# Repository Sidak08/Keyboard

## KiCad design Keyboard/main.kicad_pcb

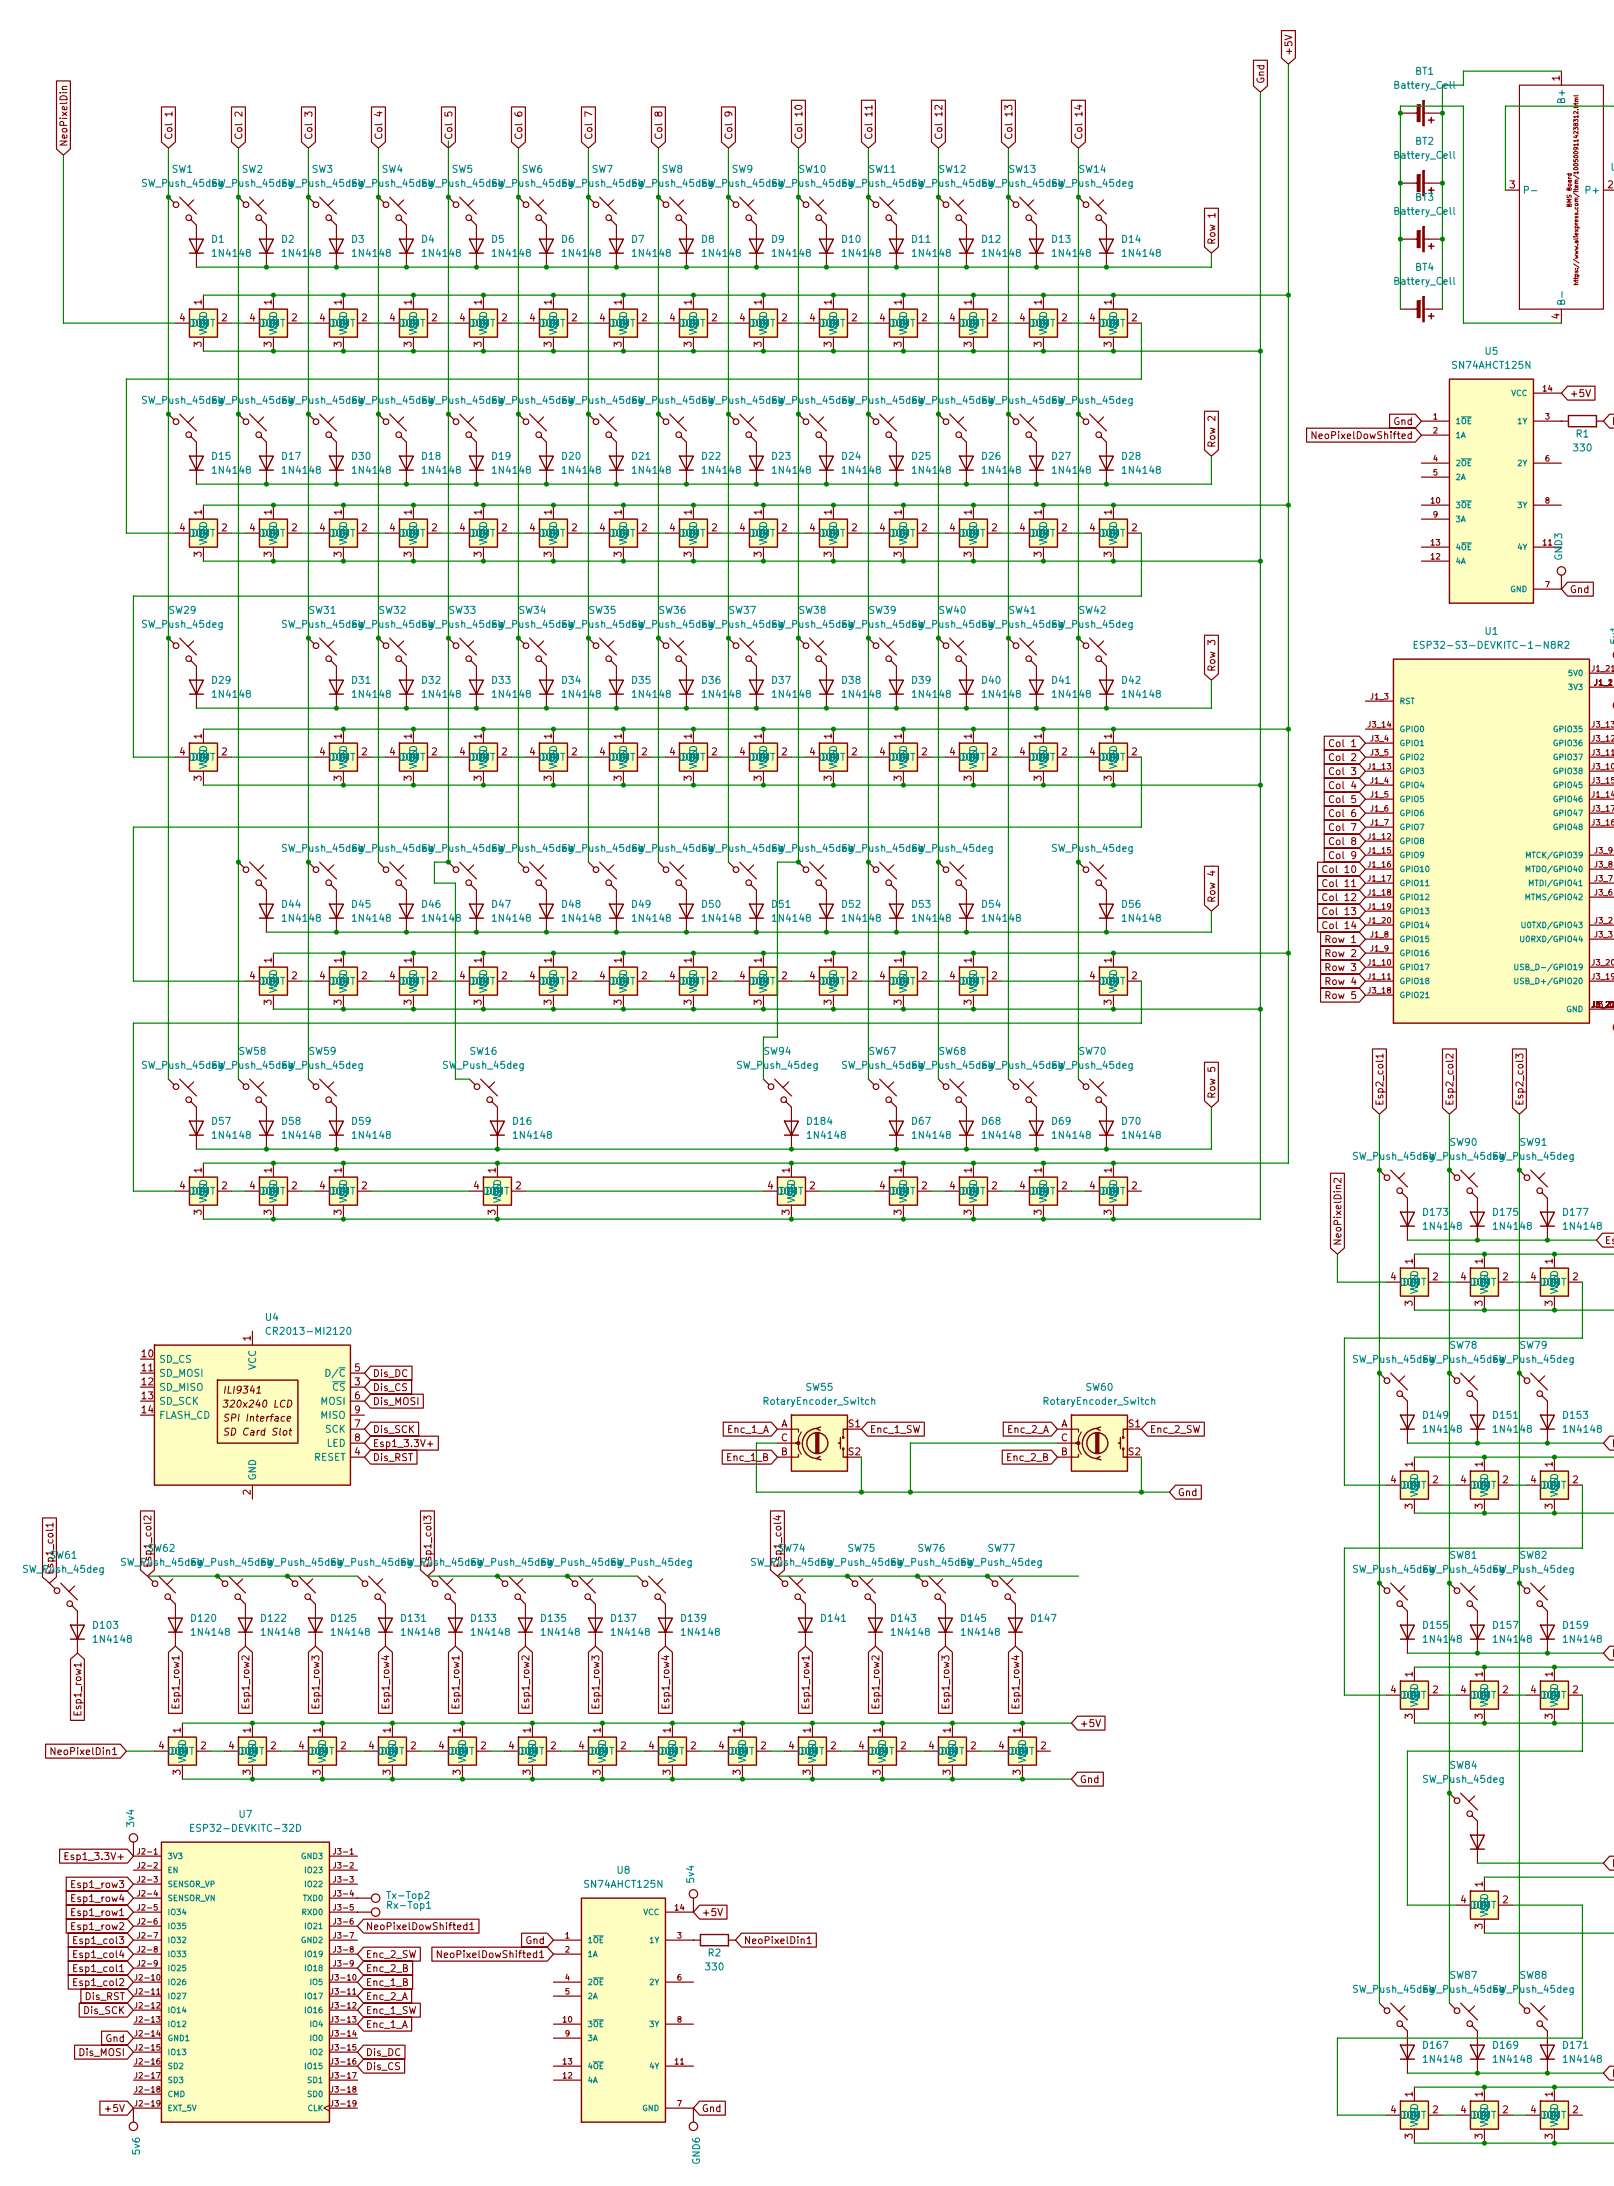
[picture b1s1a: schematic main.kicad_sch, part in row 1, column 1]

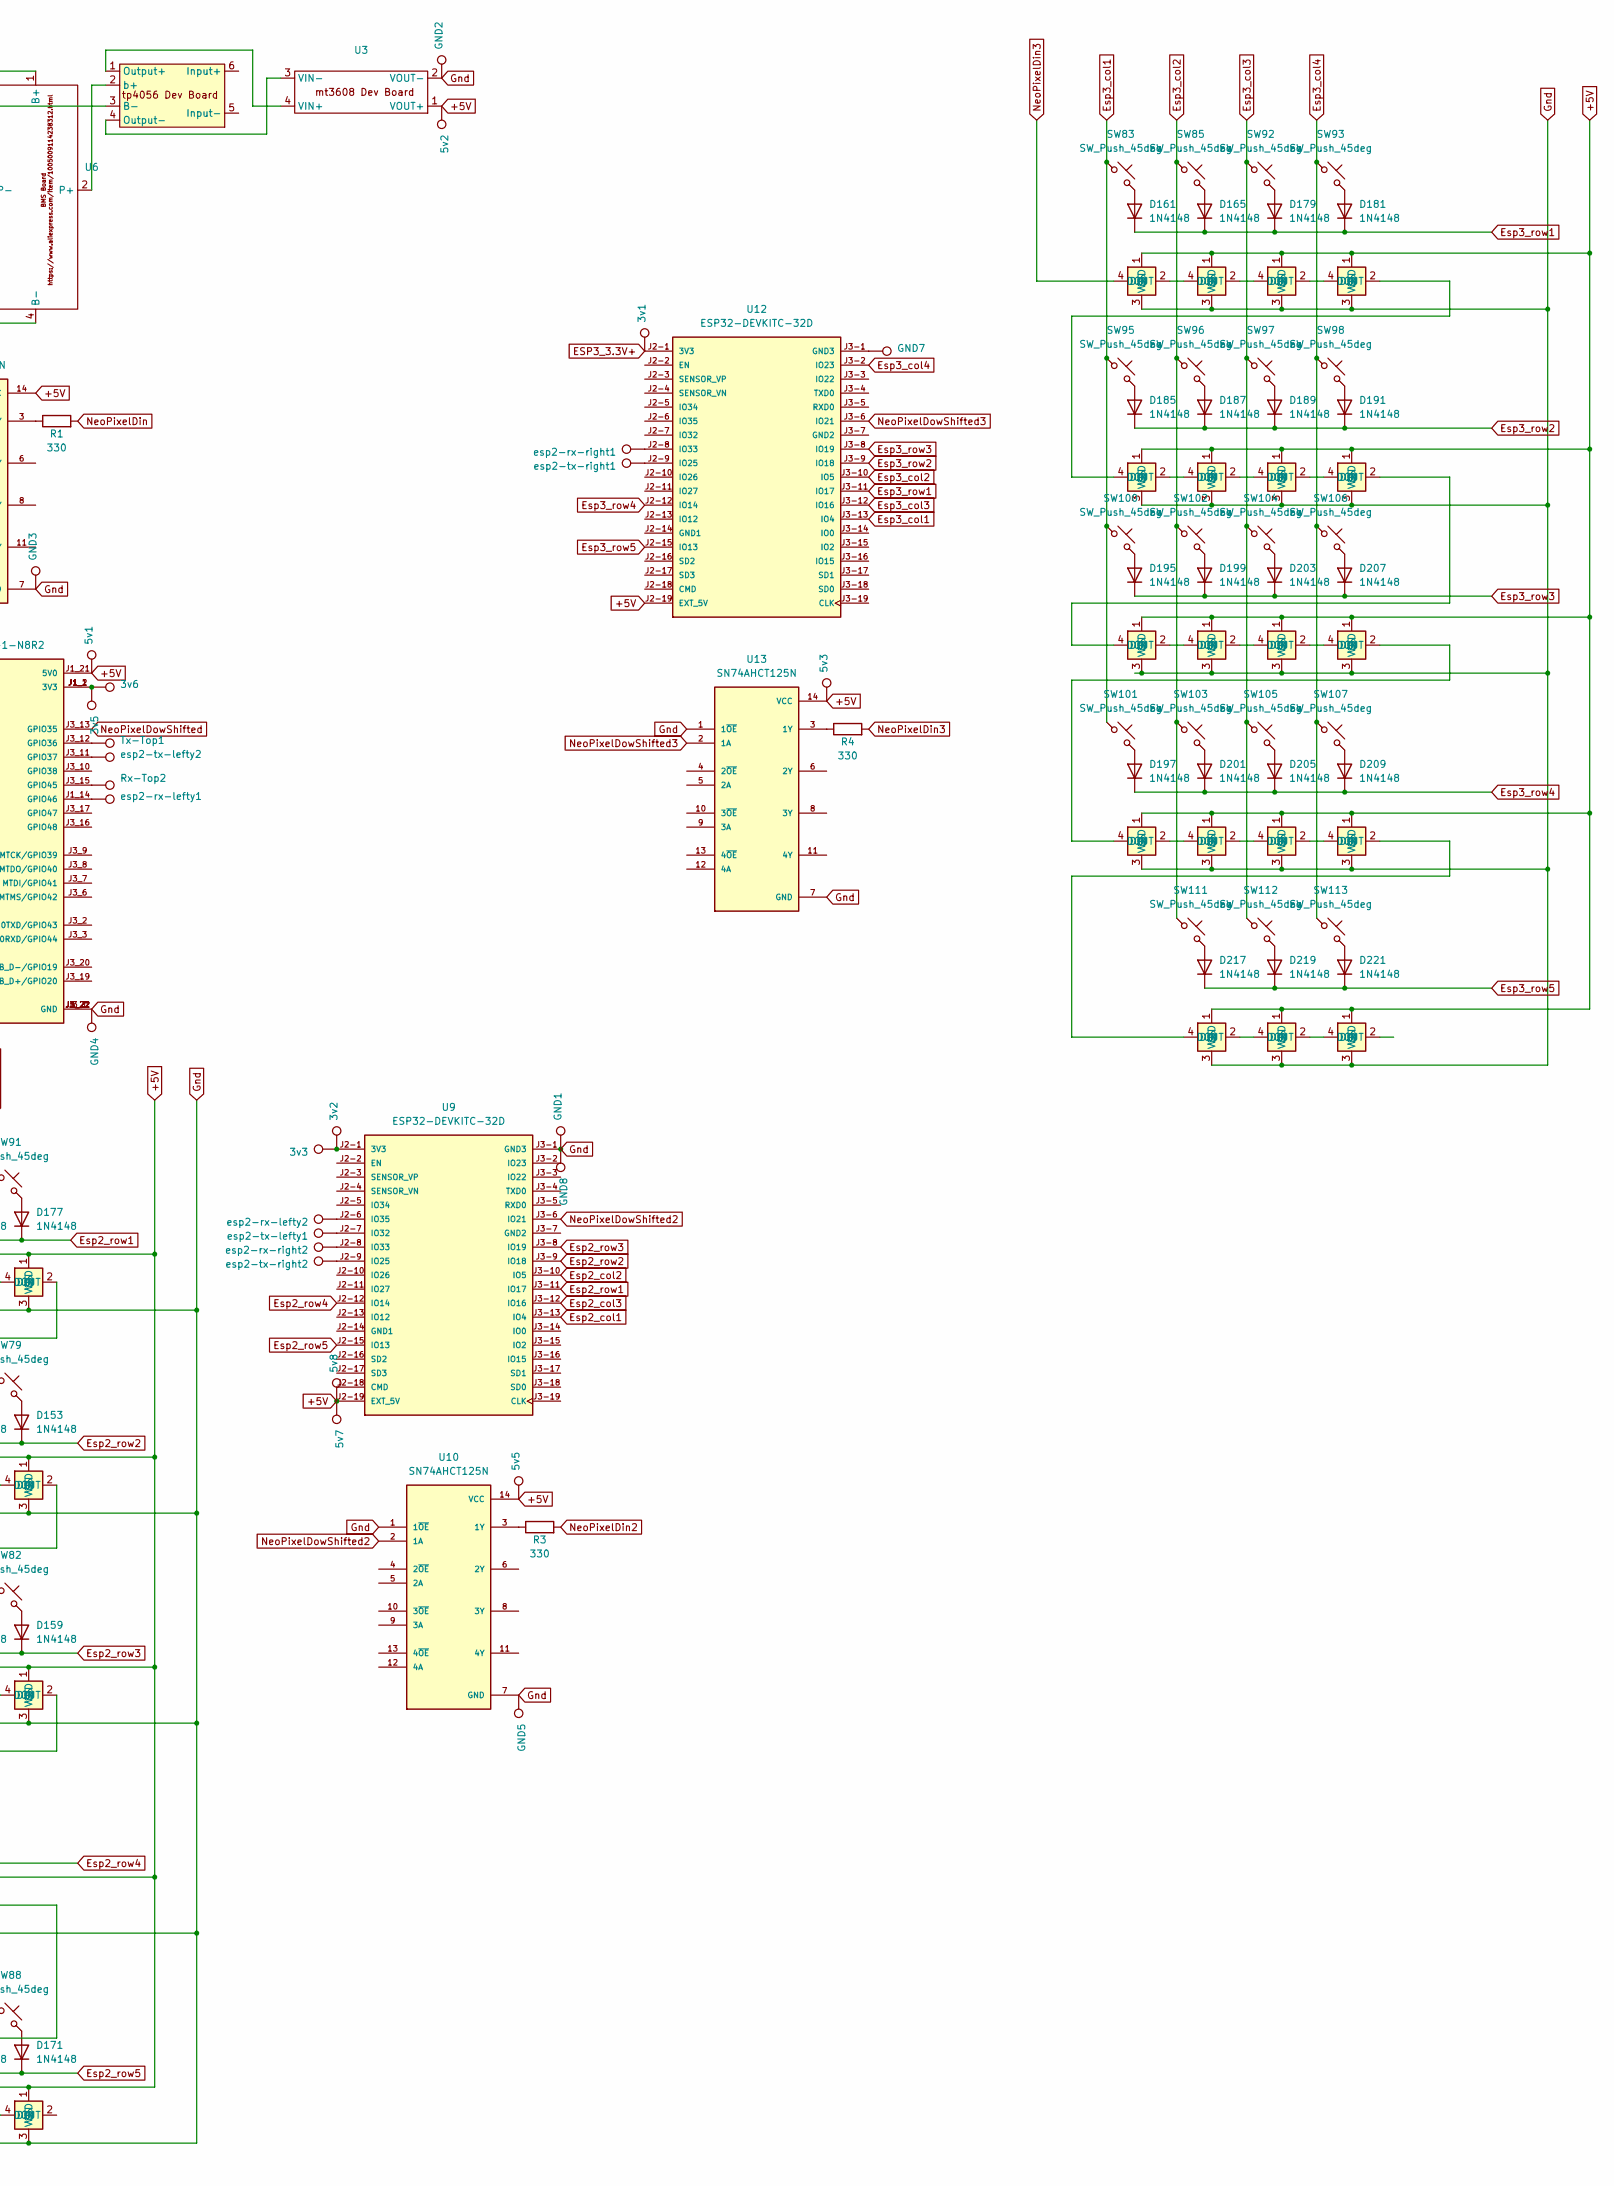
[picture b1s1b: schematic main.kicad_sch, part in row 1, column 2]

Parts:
3v1, 3v2, 3v3, 3v4, 3v5, 3v6, 5v1, 5v2, 5v3, 5v4, 5v5, 5v6, 5v7, 5v8: TestPoint; TestPoint_Pad_4.0x4.0mm
BT1, BT2, BT3, BT4: Battery_Cell; 26650CellType
D1, D2, D3, D4, D5, D6, D7, D8, D9, D10, D11, D12, D13, D14, D15, D16, D17, D18, D19, D20, D21, D22, D23, D24, D25, D26, D27, D28, D29, D30, D31, D32, D33, D34, D35, D36, D37, D38, D39, D40, D41, D42, D44, D45, D46, D47, D48, D49, D50, D51, D52, D53, D54, D56, D57, D58, D59, D67, D68, D69, D70, D103, D120, D122, D125, D131, D133, D135, D137, D139, D141, D143, D145, D147, D149, D151, D153, D155, D157, D159, D161, D163, D165, D167, D169, D171, D173, D175, D177, D179, D181, D184, D185, D187, D189, D191, D195, D197, D199, D201, D203, D205, D207, D209, D217, D219, D221: 1N4148; D_DO-35_SOD27_P7.62mm_Horizontal
D43, D55, D60, D61, D62, D63, D64, D65, D66, D71, D72, D73, D74, D75, D76, D77, D78, D79, D80, D81, D82, D83, D84, D85, D86, D87, D88, D89, D90, D91, D92, D93, D94, D95, D96, D97, D98, D99, D100, D101, D102, D104, D105, D106, D107, D108, D109, D110, D111, D112, D113, D114, D115, D116, D117, D118, D119, D121, D123, D124, D126, D127, D128, D129, D130, D132, D134, D136, D138, D140, D142, D144, D146, D148, D150, D152, D154, D156, D158, D160, D162, D164, D166, D168, D170, D172, D174, D176, D178, D180, D182, D183, D186, D188, D190, D192, D196, D198, D200, D202, D204, D206, D208, D210, D218, D220, D222: WS2812B; LED_SK6812-E
GND1, GND2, GND3, GND4, GND5, GND6, GND7, GND8: TestPoint; TestPoint_Pad_4.0x4.0mm
R1, R2, R3, R4: 330; R_Axial_DIN0207_L6.3mm_D2.5mm_P7.62mm_Horizontal
Rx-Top1, Rx-Top2: TestPoint; TestPoint_Pad_4.0x4.0mm
SW1, SW2, SW3, SW4, SW5, SW6, SW7, SW8, SW9, SW10, SW11, SW12, SW13, SW17, SW18, SW19, SW20, SW21, SW22, SW23, SW24, SW25, SW26, SW27, SW30, SW31, SW32, SW33, SW34, SW35, SW36, SW37, SW38, SW39, SW40, SW41, SW43, SW45, SW46, SW47, SW48, SW49, SW50, SW51, SW52, SW53, SW54, SW61, SW62, SW63, SW64, SW65, SW66, SW71, SW72, SW73, SW74, SW75, SW76, SW77, SW78, SW79, SW80, SW81, SW82, SW83, SW84, SW85, SW86, SW87, SW88, SW89, SW90, SW91, SW92, SW93, SW95, SW96, SW97, SW98, SW100, SW101, SW102, SW103, SW104, SW105, SW106, SW107, SW112, SW113: SW_Push_45deg; Kailh-PG1350-1u-NoLED
SW14, SW111: SW_Push_45deg; Kailh-PG1350-2u-NoLED
SW15, SW28: SW_Push_45deg; Kailh-PG1350-1.5u-NoLED
SW16, SW44, SW56, SW67, SW94: SW_Push_45deg; Kailh-PG1350-2.5u
SW29: SW_Push_45deg; Kailh-PG1350-1.75u-NoLED
SW42: SW_Push_45deg; Kailh-PG1350-2.25u-NoLED
SW55, SW60: RotaryEncoder_Switch; RotaryEncoder_Alps_EC11E-Switch_Vertical_H20mm
SW57, SW58, SW59, SW68, SW69, SW70: SW_Push_45deg; Kailh-PG1350-1.25u-NoLED
Tx-Top1, Tx-Top2: TestPoint; TestPoint_Pad_4.0x4.0mm
U1: ESP32-S3-DEVKITC-1-N8R2; XCVR_ESP32-S3-DEVKITC-1-N8R2; PARTREV V1
U2: tp4056 Dev Board
U3: mt3608KeepOut
U4: CR2013-MI2120
U5, U8, U10, U13: SN74AHCT125N; DIP794W45P254L1930H508Q14; PARTREV Q
U6: BmsBoardKeepOut
U7, U9, U12: ESP32-DEVKITC-32D; MODULE_ESP32-DEVKITC-32D; PARTREV V4
esp2-rx-lefty1, esp2-rx-lefty2, esp2-rx-right1, esp2-rx-right2, esp2-tx-lefty1, esp2-tx-lefty2, esp2-tx-right1, esp2-tx-right2: TestPoint; TestPoint_Pad_4.0x4.0mm

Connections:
+5V: 5v1.1, 5v2.1, 5v3.1, 5v4.1, 5v5.1, 5v6.1, 5v7.1, 5v8.1, D43.1 (VDD), D55.1 (VDD), D60.1 (VDD), D61.1 (VDD), D62.1 (VDD), D63.1 (VDD), D64.1 (VDD), D65.1 (VDD), D66.1 (VDD), D71.1 (VDD), D72.1 (VDD), D73.1 (VDD), D74.1 (VDD), D75.1 (VDD), D76.1 (VDD), D77.1 (VDD), D78.1 (VDD), D79.1 (VDD), D80.1 (VDD), D81.1 (VDD), D82.1 (VDD), D83.1 (VDD), D84.1 (VDD), D85.1 (VDD), D86.1 (VDD), D87.1 (VDD), D88.1 (VDD), D89.1 (VDD), D90.1 (VDD), D91.1 (VDD), D92.1 (VDD), D93.1 (VDD), D94.1 (VDD), D95.1 (VDD), D96.1 (VDD), D97.1 (VDD), D98.1 (VDD), D99.1 (VDD), D100.1 (VDD), D101.1 (VDD), D102.1 (VDD), D104.1 (VDD), D105.1 (VDD), D106.1 (VDD), D107.1 (VDD), D108.1 (VDD), D109.1 (VDD), D110.1 (VDD), D111.1 (VDD), D112.1 (VDD), D113.1 (VDD), D114.1 (VDD), D115.1 (VDD), D116.1 (VDD), D117.1 (VDD), D118.1 (VDD), D119.1 (VDD), D121.1 (VDD), D123.1 (VDD), D124.1 (VDD), D126.1 (VDD), D127.1 (VDD), D128.1 (VDD), D129.1 (VDD), D130.1 (VDD), D132.1 (VDD), D134.1 (VDD), D136.1 (VDD), D138.1 (VDD), D140.1 (VDD), D142.1 (VDD), D144.1 (VDD), D146.1 (VDD), D148.1 (VDD), D150.1 (VDD), D152.1 (VDD), D154.1 (VDD), D156.1 (VDD), D158.1 (VDD), D160.1 (VDD), D162.1 (VDD), D164.1 (VDD), D166.1 (VDD), D168.1 (VDD), D170.1 (VDD), D172.1 (VDD), D174.1 (VDD), D176.1 (VDD), D178.1 (VDD), D180.1 (VDD), D182.1 (VDD), D183.1 (VDD), D186.1 (VDD), D188.1 (VDD), D190.1 (VDD), D192.1 (VDD), D196.1 (VDD), D198.1 (VDD), D200.1 (VDD), D202.1 (VDD), D204.1 (VDD), D206.1 (VDD), D208.1 (VDD), D210.1 (VDD), D218.1 (VDD), D220.1 (VDD), D222.1 (VDD), U1.J1_21 (5V0), U3.1 (VOUT+), U5.14 (VCC), U7.J2-19 (EXT_5V), U8.14 (VCC), U9.J2-19 (EXT_5V), U10.14 (VCC), U12.J2-19 (EXT_5V), U13.14 (VCC)
Col 1: SW1.1, SW15.1, SW29.1, SW57.1, U1.J3_4 (GPIO1)
Col 2: SW2.1, SW17.1, SW44.1, SW58.1, U1.J3_5 (GPIO2)
Col 3: SW3.1, SW30.1, SW31.1, SW45.1, SW59.1, U1.J1_13 (GPIO3)
Col 4: SW4.1, SW18.1, SW32.1, SW46.1, U1.J1_4 (GPIO4)
Col 5: SW5.1, SW16.1, SW19.1, SW33.1, SW47.1, U1.J1_5 (GPIO5)
Col 6: SW6.1, SW20.1, SW34.1, SW48.1, U1.J1_6 (GPIO6)
Col 7: SW7.1, SW21.1, SW35.1, SW49.1, U1.J1_7 (GPIO7)
Col 8: SW8.1, SW22.1, SW36.1, SW50.1, U1.J1_12 (GPIO8)
Col 9: SW9.1, SW23.1, SW37.1, SW51.1, U1.J1_15 (GPIO9)
Col 10: SW10.1, SW24.1, SW38.1, SW52.1, SW94.1, U1.J1_16 (GPIO10)
Col 11: SW11.1, SW25.1, SW39.1, SW53.1, SW67.1, U1.J1_17 (GPIO11)
Col 12: SW12.1, SW26.1, SW40.1, SW54.1, SW68.1, U1.J1_18 (GPIO12)
Col 13: SW13.1, SW27.1, SW41.1, SW69.1, U1.J1_19 (GPIO13)
Col 14: SW14.1, SW28.1, SW42.1, SW56.1, SW70.1, U1.J1_20 (GPIO14)
Dis_CS: U4.3 (~CS), U7.J3-16 (IO15)
Dis_DC: U4.5 (D/~C), U7.J3-15 (IO2)
Dis_MOSI: U4.6 (MOSI), U7.J2-15 (IO13)
Dis_RST: U4.4 (RESET), U7.J2-11 (IO27)
Dis_SCK: U4.7 (SCK), U7.J2-12 (IO14)
ESP3_3.3V+: 3v1.1, U12.J2-1 (3V3)
Enc_1_A: SW55.A, U7.J3-13 (IO4)
Enc_1_B: SW55.B, U7.J3-10 (IO5)
Enc_1_SW: SW55.S1, U7.J3-12 (IO16)
Enc_2_A: SW60.A, U7.J3-11 (IO17)
Enc_2_B: SW60.B, U7.J3-9 (IO18)
Enc_2_SW: SW60.S1, U7.J3-8 (IO19)
Esp1_3.3V+: 3v4.1, U4.8 (LED), U7.J2-1 (3V3)
Esp1_col1: SW61.1, U7.J2-9 (IO25)
Esp1_col2: SW62.1, SW63.1, SW64.1, SW65.1, U7.J2-10 (IO26)
Esp1_col3: SW66.1, SW71.1, SW72.1, SW73.1, U7.J2-7 (IO32)
Esp1_col4: SW74.1, SW75.1, SW76.1, SW77.1, U7.J2-8 (IO33)
Esp1_row1: D103.1 (K), D120.1 (K), D133.1 (K), D141.1 (K), U7.J2-5 (IO34)
Esp1_row2: D122.1 (K), D135.1 (K), D143.1 (K), U7.J2-6 (IO35)
Esp1_row3: D125.1 (K), D137.1 (K), D145.1 (K), U7.J2-3 (SENSOR_VP)
Esp1_row4: D131.1 (K), D139.1 (K), D147.1 (K), U7.J2-4 (SENSOR_VN)
Esp2_col1: SW43.1, SW80.1, SW86.1, SW89.1, U9.J3-13 (IO4)
Esp2_col2: SW78.1, SW81.1, SW84.1, SW87.1, SW90.1, U9.J3-10 (IO5)
Esp2_col3: SW79.1, SW82.1, SW88.1, SW91.1, U9.J3-12 (IO16)
Esp2_row1: D173.1 (K), D175.1 (K), D177.1 (K), U9.J3-11 (IO17)
Esp2_row2: D149.1 (K), D151.1 (K), D153.1 (K), U9.J3-9 (IO18)
Esp2_row3: D155.1 (K), D157.1 (K), D159.1 (K), U9.J3-8 (IO19)
Esp2_row4: D163.1 (K), U9.J2-12 (IO14)
Esp2_row5: D167.1 (K), D169.1 (K), D171.1 (K), U9.J2-15 (IO13)
Esp3_col1: SW83.1, SW95.1, SW100.1, SW101.1, U12.J3-13 (IO4)
Esp3_col2: SW85.1, SW96.1, SW102.1, SW103.1, SW111.1, U12.J3-10 (IO5)
Esp3_col3: SW92.1, SW97.1, SW104.1, SW105.1, SW112.1, U12.J3-12 (IO16)
Esp3_col4: SW93.1, SW98.1, SW106.1, SW107.1, SW113.1, U12.J3-2 (IO23)
Esp3_row1: D161.1 (K), D165.1 (K), D179.1 (K), D181.1 (K), U12.J3-11 (IO17)
Esp3_row2: D185.1 (K), D187.1 (K), D189.1 (K), D191.1 (K), U12.J3-9 (IO18)
Esp3_row3: D195.1 (K), D199.1 (K), D203.1 (K), D207.1 (K), U12.J3-8 (IO19)
Esp3_row4: D197.1 (K), D201.1 (K), D205.1 (K), D209.1 (K), U12.J2-12 (IO14)
Esp3_row5: D217.1 (K), D219.1 (K), D221.1 (K), U12.J2-15 (IO13)
Gnd: D43.3 (VSS), D55.3 (VSS), D60.3 (VSS), D61.3 (VSS), D62.3 (VSS), D63.3 (VSS), D64.3 (VSS), D65.3 (VSS), D66.3 (VSS), D71.3 (VSS), D72.3 (VSS), D73.3 (VSS), D74.3 (VSS), D75.3 (VSS), D76.3 (VSS), D77.3 (VSS), D78.3 (VSS), D79.3 (VSS), D80.3 (VSS), D81.3 (VSS), D82.3 (VSS), D83.3 (VSS), D84.3 (VSS), D85.3 (VSS), D86.3 (VSS), D87.3 (VSS), D88.3 (VSS), D89.3 (VSS), D90.3 (VSS), D91.3 (VSS), D92.3 (VSS), D93.3 (VSS), D94.3 (VSS), D95.3 (VSS), D96.3 (VSS), D97.3 (VSS), D98.3 (VSS), D99.3 (VSS), D100.3 (VSS), D101.3 (VSS), D102.3 (VSS), D104.3 (VSS), D105.3 (VSS), D106.3 (VSS), D107.3 (VSS), D108.3 (VSS), D109.3 (VSS), D110.3 (VSS), D111.3 (VSS), D112.3 (VSS), D113.3 (VSS), D114.3 (VSS), D115.3 (VSS), D116.3 (VSS), D117.3 (VSS), D118.3 (VSS), D119.3 (VSS), D121.3 (VSS), D123.3 (VSS), D124.3 (VSS), D126.3 (VSS), D127.3 (VSS), D128.3 (VSS), D129.3 (VSS), D130.3 (VSS), D132.3 (VSS), D134.3 (VSS), D136.3 (VSS), D138.3 (VSS), D140.3 (VSS), D142.3 (VSS), D144.3 (VSS), D146.3 (VSS), D148.3 (VSS), D150.3 (VSS), D152.3 (VSS), D154.3 (VSS), D156.3 (VSS), D158.3 (VSS), D160.3 (VSS), D162.3 (VSS), D164.3 (VSS), D166.3 (VSS), D168.3 (VSS), D170.3 (VSS), D172.3 (VSS), D174.3 (VSS), D176.3 (VSS), D178.3 (VSS), D180.3 (VSS), D182.3 (VSS), D183.3 (VSS), D186.3 (VSS), D188.3 (VSS), D190.3 (VSS), D192.3 (VSS), D196.3 (VSS), D198.3 (VSS), D200.3 (VSS), D202.3 (VSS), D204.3 (VSS), D206.3 (VSS), D208.3 (VSS), D210.3 (VSS), D218.3 (VSS), D220.3 (VSS), D222.3 (VSS), GND1.1, GND2.1, GND3.1, GND4.1, GND5.1, GND6.1, GND8.1, SW55.C, SW55.S2, SW60.C, SW60.S2, U1.J1_22 (GND), U1.J3_1 (GND), U1.J3_21 (GND), U1.J3_22 (GND), U3.2 (VOUT-), U5.1 (1~OE), U5.7 (GND), U7.J2-14 (GND1), U8.1 (1~OE), U8.7 (GND), U9.J3-1 (GND3), U10.1 (1~OE), U10.7 (GND), U13.1 (1~OE), U13.7 (GND)
NeoPixelDin: D90.4 (DIN), R1.2
NeoPixelDin1: D115.4 (DIN), R2.2
NeoPixelDin2: D174.4 (DIN), R3.2
NeoPixelDin3: D162.4 (DIN), R4.2
NeoPixelDowShifted: U1.J3_13 (GPIO35), U5.2 (1A)
NeoPixelDowShifted1: U7.J3-6 (IO21), U8.2 (1A)
NeoPixelDowShifted2: U9.J3-6 (IO21), U10.2 (1A)
NeoPixelDowShifted3: U12.J3-6 (IO21), U13.2 (1A)
unnamed: 3v5.1, 3v6.1, U1.J1_1 (3V3), U1.J1_2 (3V3)
unnamed: BT1.1 (+), BT2.1 (+), BT3.1 (+), BT4.1 (+), U6.1 (B+)
unnamed: BT1.2 (-), BT2.2 (-), BT3.2 (-), BT4.2 (-), U6.4 (B-)
unnamed: D1.2 (A), SW1.2
unnamed: D2.2 (A), SW2.2
unnamed: D3.2 (A), SW3.2
unnamed: D4.2 (A), SW4.2
unnamed: D5.2 (A), SW5.2
unnamed: D6.2 (A), SW6.2
unnamed: D7.2 (A), SW7.2
unnamed: D8.2 (A), SW8.2
unnamed: D9.2 (A), SW9.2
unnamed: D10.2 (A), SW10.2
unnamed: D11.2 (A), SW11.2
unnamed: D12.2 (A), SW12.2
unnamed: D13.2 (A), SW13.2
unnamed: D14.2 (A), SW14.2
unnamed: D15.2 (A), SW15.2
unnamed: D16.2 (A), SW16.2
unnamed: D17.2 (A), SW17.2
unnamed: D18.2 (A), SW18.2
unnamed: D19.2 (A), SW19.2
unnamed: D20.2 (A), SW20.2
unnamed: D21.2 (A), SW21.2
unnamed: D22.2 (A), SW22.2
unnamed: D23.2 (A), SW23.2
unnamed: D24.2 (A), SW24.2
unnamed: D25.2 (A), SW25.2
unnamed: D26.2 (A), SW26.2
unnamed: D27.2 (A), SW27.2
unnamed: D28.2 (A), SW28.2
unnamed: D29.2 (A), SW29.2
unnamed: D30.2 (A), SW30.2
unnamed: D31.2 (A), SW31.2
unnamed: D32.2 (A), SW32.2
unnamed: D33.2 (A), SW33.2
unnamed: D34.2 (A), SW34.2
unnamed: D35.2 (A), SW35.2
unnamed: D36.2 (A), SW36.2
unnamed: D37.2 (A), SW37.2
unnamed: D38.2 (A), SW38.2
unnamed: D39.2 (A), SW39.2
unnamed: D40.2 (A), SW40.2
unnamed: D41.2 (A), SW41.2
unnamed: D42.2 (A), SW42.2
unnamed: D43.4 (DIN), D90.2 (DOUT)
unnamed: D43.2 (DOUT), D55.4 (DIN)
unnamed: D44.2 (A), SW44.2
unnamed: D45.2 (A), SW45.2
unnamed: D46.2 (A), SW46.2
unnamed: D47.2 (A), SW47.2
unnamed: D48.2 (A), SW48.2
unnamed: D49.2 (A), SW49.2
unnamed: D50.2 (A), SW50.2
unnamed: D51.2 (A), SW51.2
unnamed: D52.2 (A), SW52.2
unnamed: D53.2 (A), SW53.2
unnamed: D54.2 (A), SW54.2
unnamed: D55.2 (DOUT), D60.4 (DIN)
unnamed: D56.2 (A), SW56.2
unnamed: D57.2 (A), SW57.2
unnamed: D58.2 (A), SW58.2
unnamed: D59.2 (A), SW59.2
unnamed: D60.2 (DOUT), D61.4 (DIN)
unnamed: D61.2 (DOUT), D62.4 (DIN)
unnamed: D62.2 (DOUT), D63.4 (DIN)
unnamed: D63.2 (DOUT), D64.4 (DIN)
unnamed: D64.2 (DOUT), D65.4 (DIN)
unnamed: D65.2 (DOUT), D66.4 (DIN)
unnamed: D66.2 (DOUT), D71.4 (DIN)
unnamed: D67.2 (A), SW67.2
unnamed: D68.2 (A), SW68.2
unnamed: D69.2 (A), SW69.2
unnamed: D70.2 (A), SW70.2
unnamed: D71.2 (DOUT), D72.4 (DIN)
unnamed: D72.2 (DOUT), D73.4 (DIN)
unnamed: D73.2 (DOUT), D74.4 (DIN)
unnamed: D74.2 (DOUT), D75.4 (DIN)
unnamed: D75.2 (DOUT), D76.4 (DIN)
unnamed: D76.2 (DOUT), D77.4 (DIN)
unnamed: D77.2 (DOUT), D78.4 (DIN)
unnamed: D78.2 (DOUT), D79.4 (DIN)
unnamed: D79.2 (DOUT), D80.4 (DIN)
unnamed: D80.2 (DOUT), D81.4 (DIN)
unnamed: D81.2 (DOUT), D82.4 (DIN)
unnamed: D82.2 (DOUT), D83.4 (DIN)
unnamed: D83.2 (DOUT), D84.4 (DIN)
unnamed: D84.2 (DOUT), D85.4 (DIN)
unnamed: D85.2 (DOUT), D86.4 (DIN)
unnamed: D86.2 (DOUT), D87.4 (DIN)
unnamed: D87.2 (DOUT), D88.4 (DIN)
unnamed: D88.2 (DOUT), D89.4 (DIN)
unnamed: D89.2 (DOUT), D91.4 (DIN)
unnamed: D91.2 (DOUT), D92.4 (DIN)
unnamed: D92.2 (DOUT), D93.4 (DIN)
unnamed: D93.2 (DOUT), D94.4 (DIN)
unnamed: D94.2 (DOUT), D95.4 (DIN)
unnamed: D95.2 (DOUT), D96.4 (DIN)
unnamed: D96.2 (DOUT), D97.4 (DIN)
unnamed: D97.2 (DOUT), D98.4 (DIN)
unnamed: D98.2 (DOUT), D99.4 (DIN)
unnamed: D99.2 (DOUT), D100.4 (DIN)
unnamed: D100.2 (DOUT), D101.4 (DIN)
unnamed: D101.2 (DOUT), D102.4 (DIN)
unnamed: D102.2 (DOUT), D104.4 (DIN)
unnamed: D103.2 (A), SW61.2
unnamed: D104.2 (DOUT), D105.4 (DIN)
unnamed: D105.2 (DOUT), D106.4 (DIN)
unnamed: D106.2 (DOUT), D107.4 (DIN)
unnamed: D107.2 (DOUT), D108.4 (DIN)
unnamed: D108.2 (DOUT), D109.4 (DIN)
unnamed: D109.2 (DOUT), D110.4 (DIN)
unnamed: D110.2 (DOUT), D111.4 (DIN)
unnamed: D111.2 (DOUT), D112.4 (DIN)
unnamed: D112.2 (DOUT), D113.4 (DIN)
unnamed: D113.2 (DOUT), D114.4 (DIN)
unnamed: D114.2 (DOUT), D116.4 (DIN)
unnamed: D115.2 (DOUT), D121.4 (DIN)
unnamed: D116.2 (DOUT), D117.4 (DIN)
unnamed: D117.2 (DOUT), D118.4 (DIN)
unnamed: D118.2 (DOUT), D119.4 (DIN)
unnamed: D119.2 (DOUT), D123.4 (DIN)
unnamed: D120.2 (A), SW62.2
unnamed: D121.2 (DOUT), D124.4 (DIN)
unnamed: D122.2 (A), SW63.2
unnamed: D123.2 (DOUT), D183.4 (DIN)
unnamed: D124.2 (DOUT), D126.4 (DIN)
unnamed: D125.2 (A), SW64.2
unnamed: D126.2 (DOUT), D132.4 (DIN)
unnamed: D127.4 (DIN), D183.2 (DOUT)
unnamed: D127.2 (DOUT), D128.4 (DIN)
unnamed: D128.2 (DOUT), D129.4 (DIN)
unnamed: D129.2 (DOUT), D130.4 (DIN)
unnamed: D131.2 (A), SW65.2
unnamed: D132.2 (DOUT), D134.4 (DIN)
unnamed: D133.2 (A), SW66.2
unnamed: D134.2 (DOUT), D136.4 (DIN)
unnamed: D135.2 (A), SW71.2
unnamed: D136.2 (DOUT), D138.4 (DIN)
unnamed: D137.2 (A), SW72.2
unnamed: D138.2 (DOUT), D140.4 (DIN)
unnamed: D139.2 (A), SW73.2
unnamed: D140.2 (DOUT), D142.4 (DIN)
unnamed: D141.2 (A), SW74.2
unnamed: D142.2 (DOUT), D144.4 (DIN)
unnamed: D143.2 (A), SW75.2
unnamed: D144.2 (DOUT), D146.4 (DIN)
unnamed: D145.2 (A), SW76.2
unnamed: D146.2 (DOUT), D148.4 (DIN)
unnamed: D147.2 (A), SW77.2
unnamed: D149.2 (A), SW43.2
unnamed: D150.4 (DIN), D178.2 (DOUT)
unnamed: D150.2 (DOUT), D152.4 (DIN)
unnamed: D151.2 (A), SW78.2
unnamed: D152.2 (DOUT), D154.4 (DIN)
unnamed: D153.2 (A), SW79.2
unnamed: D154.2 (DOUT), D156.4 (DIN)
unnamed: D155.2 (A), SW80.2
unnamed: D156.2 (DOUT), D158.4 (DIN)
unnamed: D157.2 (A), SW81.2
unnamed: D158.2 (DOUT), D160.4 (DIN)
unnamed: D159.2 (A), SW82.2
unnamed: D160.2 (DOUT), D164.4 (DIN)
unnamed: D161.2 (A), SW83.2
unnamed: D162.2 (DOUT), D166.4 (DIN)
unnamed: D163.2 (A), SW84.2
unnamed: D164.2 (DOUT), D168.4 (DIN)
unnamed: D165.2 (A), SW85.2
unnamed: D166.2 (DOUT), D180.4 (DIN)
unnamed: D167.2 (A), SW86.2
unnamed: D168.2 (DOUT), D170.4 (DIN)
unnamed: D169.2 (A), SW87.2
unnamed: D170.2 (DOUT), D172.4 (DIN)
unnamed: D171.2 (A), SW88.2
unnamed: D173.2 (A), SW89.2
unnamed: D174.2 (DOUT), D176.4 (DIN)
unnamed: D175.2 (A), SW90.2
unnamed: D176.2 (DOUT), D178.4 (DIN)
unnamed: D177.2 (A), SW91.2
unnamed: D179.2 (A), SW92.2
unnamed: D180.2 (DOUT), D182.4 (DIN)
unnamed: D181.2 (A), SW93.2
unnamed: D182.2 (DOUT), D186.4 (DIN)
unnamed: D184.2 (A), SW94.2
unnamed: D185.2 (A), SW95.2
unnamed: D186.2 (DOUT), D188.4 (DIN)
unnamed: D187.2 (A), SW96.2
unnamed: D188.2 (DOUT), D190.4 (DIN)
unnamed: D189.2 (A), SW97.2
unnamed: D190.2 (DOUT), D192.4 (DIN)
unnamed: D191.2 (A), SW98.2
unnamed: D192.2 (DOUT), D196.4 (DIN)
unnamed: D195.2 (A), SW100.2
unnamed: D196.2 (DOUT), D200.4 (DIN)
unnamed: D197.2 (A), SW101.2
unnamed: D198.4 (DIN), D208.2 (DOUT)
unnamed: D198.2 (DOUT), D202.4 (DIN)
unnamed: D199.2 (A), SW102.2
unnamed: D200.2 (DOUT), D204.4 (DIN)
unnamed: D201.2 (A), SW103.2
unnamed: D202.2 (DOUT), D206.4 (DIN)
unnamed: D203.2 (A), SW104.2
unnamed: D204.2 (DOUT), D208.4 (DIN)
unnamed: D205.2 (A), SW105.2
unnamed: D206.2 (DOUT), D210.4 (DIN)
unnamed: D207.2 (A), SW106.2
unnamed: D209.2 (A), SW107.2
unnamed: D210.2 (DOUT), D218.4 (DIN)
unnamed: D217.2 (A), SW111.2
unnamed: D218.2 (DOUT), D220.4 (DIN)
unnamed: D219.2 (A), SW112.2
unnamed: D220.2 (DOUT), D222.4 (DIN)
unnamed: D221.2 (A), SW113.2
unnamed: Tx-Top1.1, U1.J3_12 (GPIO36)
unnamed: U1.J3_11 (GPIO37), esp2-tx-lefty2.1
unnamed: Rx-Top2.1, U1.J3_15 (GPIO45)
unnamed: U1.J1_14 (GPIO46), esp2-rx-lefty1.1
unnamed: U2.3 (B-), U6.3 (P-)
unnamed: U2.1 (Output+), U3.4 (VIN+)
unnamed: U2.4 (Output-), U3.3 (VIN-)
unnamed: U2.2 (b+), U6.2 (P+)
unnamed: R1.1, U5.3 (1Y)
unnamed: Rx-Top1.1, U7.J3-5 (RXD0)
unnamed: Tx-Top2.1, U7.J3-4 (TXD0)
unnamed: R2.1, U8.3 (1Y)
unnamed: 3v2.1, 3v3.1, U9.J2-1 (3V3)
unnamed: U9.J2-9 (IO25), esp2-tx-right2.1
unnamed: U9.J2-7 (IO32), esp2-tx-lefty1.1
unnamed: U9.J2-8 (IO33), esp2-rx-right2.1
unnamed: U9.J2-6 (IO35), esp2-rx-lefty2.1
unnamed: R3.1, U10.3 (1Y)
unnamed: GND7.1, U12.J3-1 (GND3)
unnamed: U12.J2-9 (IO25), esp2-tx-right1.1
unnamed: U12.J2-8 (IO33), esp2-rx-right1.1
unnamed: R4.1, U13.3 (1Y)
Row 1: D1.1 (K), D2.1 (K), D3.1 (K), D4.1 (K), D5.1 (K), D6.1 (K), D7.1 (K), D8.1 (K), D9.1 (K), D10.1 (K), D11.1 (K), D12.1 (K), D13.1 (K), D14.1 (K), U1.J1_8 (GPIO15)
Row 2: D15.1 (K), D17.1 (K), D18.1 (K), D19.1 (K), D20.1 (K), D21.1 (K), D22.1 (K), D23.1 (K), D24.1 (K), D25.1 (K), D26.1 (K), D27.1 (K), D28.1 (K), D30.1 (K), U1.J1_9 (GPIO16)
Row 3: D29.1 (K), D31.1 (K), D32.1 (K), D33.1 (K), D34.1 (K), D35.1 (K), D36.1 (K), D37.1 (K), D38.1 (K), D39.1 (K), D40.1 (K), D41.1 (K), D42.1 (K), U1.J1_10 (GPIO17)
Row 4: D44.1 (K), D45.1 (K), D46.1 (K), D47.1 (K), D48.1 (K), D49.1 (K), D50.1 (K), D51.1 (K), D52.1 (K), D53.1 (K), D54.1 (K), D56.1 (K), U1.J1_11 (GPIO18)
Row 5: D16.1 (K), D57.1 (K), D58.1 (K), D59.1 (K), D67.1 (K), D68.1 (K), D69.1 (K), D70.1 (K), D184.1 (K), U1.J3_18 (GPIO21)

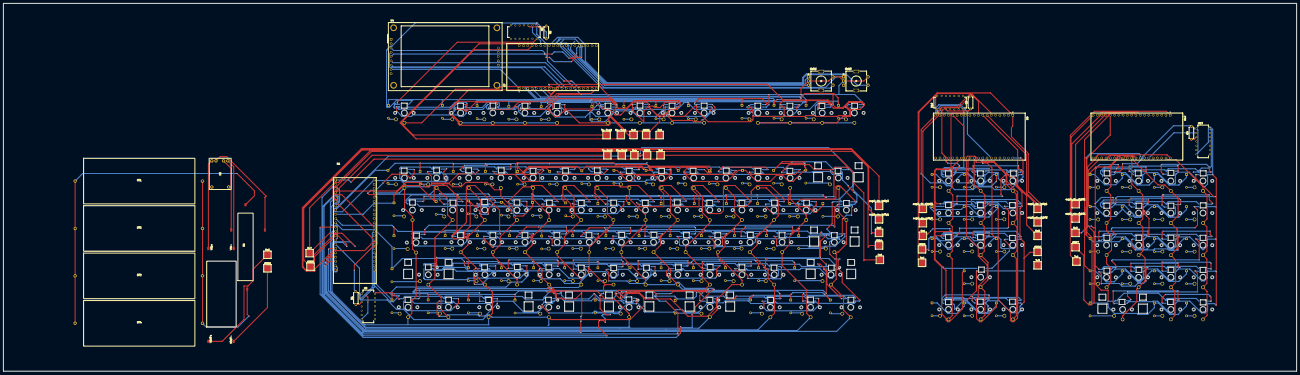
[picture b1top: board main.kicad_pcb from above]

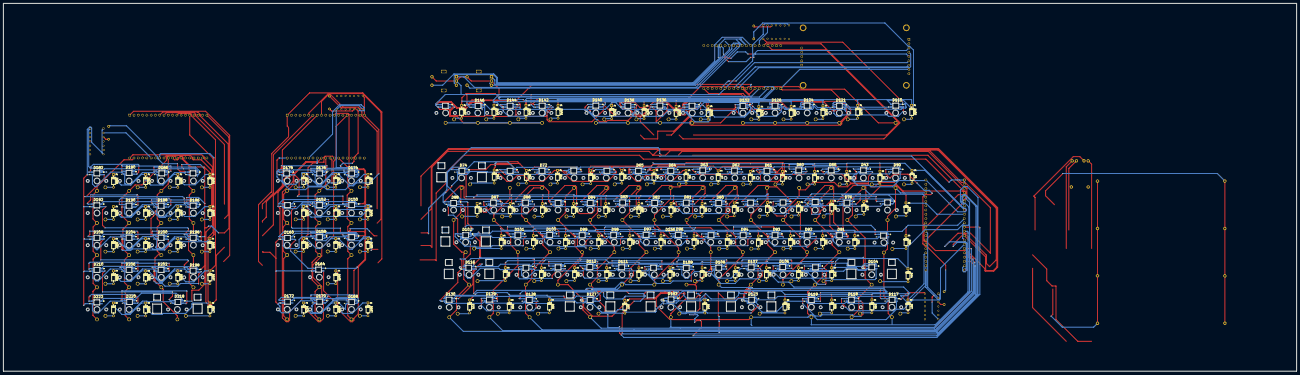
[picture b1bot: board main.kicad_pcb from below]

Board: 2 copper layers, 766.5 x 218.0 mm, 377 parts (214 on the bottom side), 302 nets.

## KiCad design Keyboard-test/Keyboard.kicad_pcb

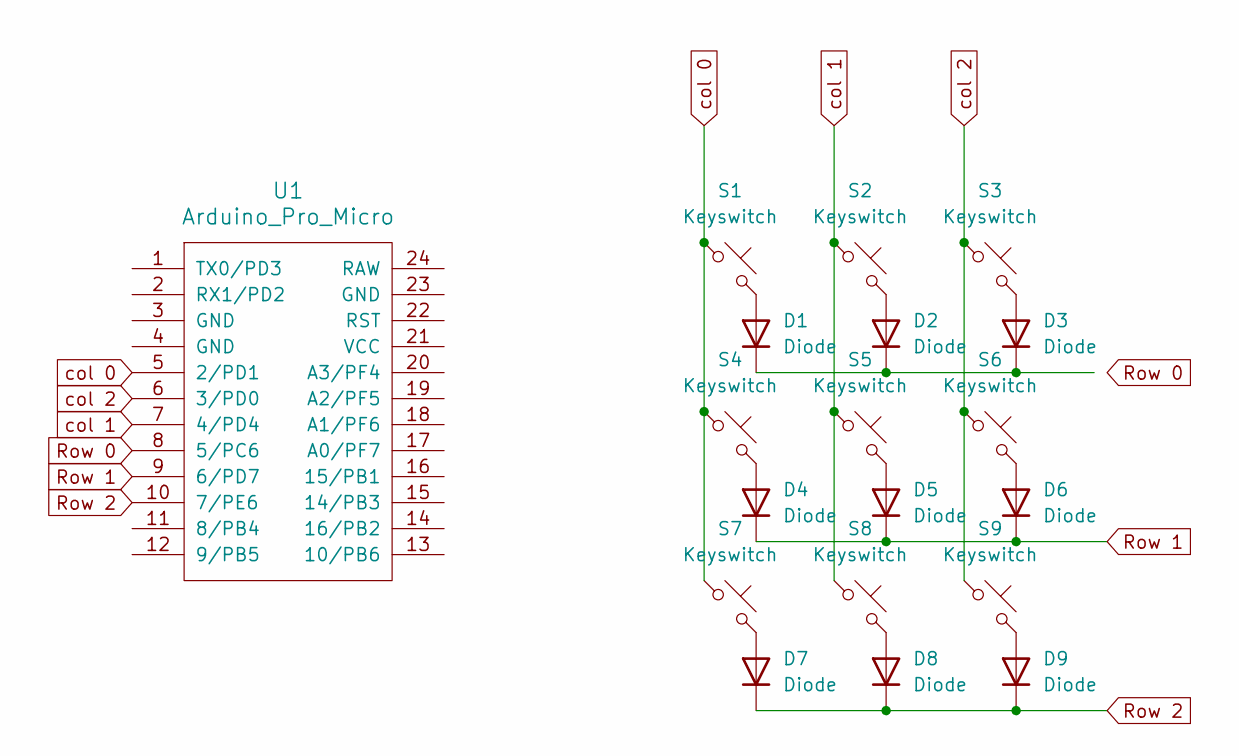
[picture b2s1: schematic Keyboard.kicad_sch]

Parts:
D1, D2, D3, D4, D5, D6, D7, D8, D9: Diode; Diode_DO-35
S1, S2, S3, S4, S5, S6, S7, S8, S9: Keyswitch; MX_PCB_1.00u
U1: Arduino_Pro_Micro

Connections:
unnamed: D1.2 (A), S1.2
unnamed: D1.1 (K), D2.1 (K), D3.1 (K)
unnamed: D2.2 (A), S2.2
unnamed: D3.2 (A), S3.2
unnamed: D4.2 (A), S4.2
unnamed: D5.2 (A), S5.2
unnamed: D6.2 (A), S6.2
unnamed: D7.2 (A), S7.2
unnamed: D8.2 (A), S8.2
unnamed: D9.2 (A), S9.2
Row 0: U1.8 (5/PC6)
Row 1: D4.1 (K), D5.1 (K), D6.1 (K), U1.9 (6/PD7)
Row 2: D7.1 (K), D8.1 (K), D9.1 (K), U1.10 (7/PE6)
col 0: S1.1, S4.1, S7.1, U1.5 (2/PD1)
col 1: S2.1, S5.1, S8.1, U1.7 (4/PD4)
col 2: S3.1, S6.1, S9.1, U1.6 (3/PD0)

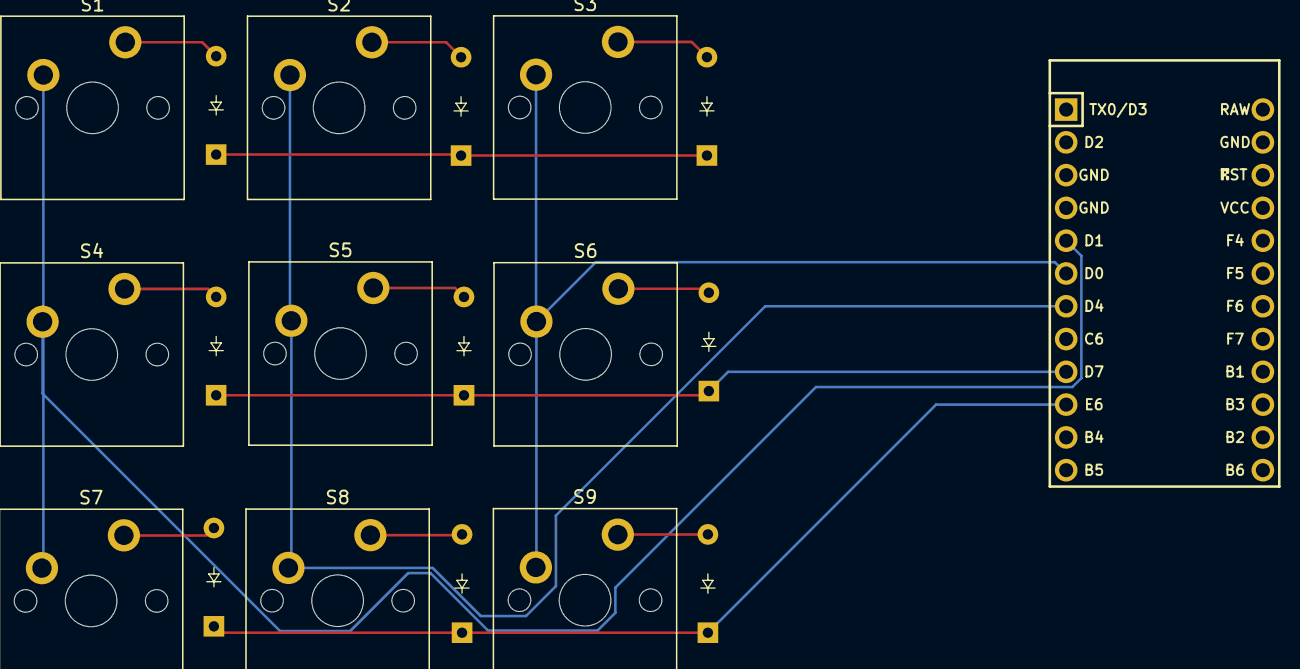
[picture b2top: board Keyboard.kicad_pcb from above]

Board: 2 copper layers, 19 parts (0 on the bottom side), 15 nets.

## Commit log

2025-06-24 base setup
2025-06-26 first day log
2025-07-02 keyboard thingy switching
2025-07-02 minor updates
2025-07-12 some changes
2025-07-14 july 12
2025-07-31 pcb done I think
2025-07-31 step file
